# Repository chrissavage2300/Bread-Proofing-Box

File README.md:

# Bread-Proofing-Box
A PID controlled bread proofing box with heater

<H3>Change log</H3>

<b>9/22/2020</b>After some consideration, I might just end up using a light bulb for a heater instead of the custom one. The one I wound by hand would be great for dehydrating stuff, but it would consume 600W! In open air, a 200W light bulb got pretty hot, so I think I may use a 40W to 60W bulb for such low temperatures. I dont know where else I could look for heater.

<b>9/19/2020</b> Output is now connected to the PID loop in code. After some minor adjustments on the bench, it seems to be working great!

<b>8/3/2020</b> Mile stone reached! I managed to dim a light after a few days worth of troubleshooting, I found out I needed a 4 Quad TRIAC. So the main TRIAC is now a BT138-600. I also had to change the output from timer 2 to stay low and then go high, essentially making this a constant off time circuit. Once I got that figured out, I then saw the proper sine waves!

<b>5/29/2020</b> Rotary Encoder Works. Timer 1 also works. Outputs also work. Waiting on Rev B.

<b>5/24/2020</b> A major error was found. The power IC's IC2 and 3 are backwards. I thought I fixed it from an older revision, but guess not. Either way the current board is a dud :(. Also the transformer doesnt fit either, so this is now in pause while I wait and do another PCB revision.

<b>5/11/2020</b> Added in documents to show heatsink calculations along with heater wire calculations

<b>5/11/2020</b> Idea: Timer function on screen, count down? Time Remaining. Have buzzer go off when "done". This would be useful for a hydrate function.

<b>5/08/2020</b>- Board sent to PCB maker.

<b>5/03/2020</b>-Initially started with a PIC16F15356 but realized that it may need more memory for running a glcd. Also may need more processing power and higher clock frequency's so I may go with a 18F26Q10. 

Also I may rethink the heater. It kind of smells like burning plastic when on, so I may design my own using Nichrome 60 wire

<b>4/28/2020</b>-Got mechanical encoder code working. Also stuck the heater in the box to get an idea of what kind of temps I could expect. It seemed to max out to around 114F and then the shutoff kicked in slightly after that. So the max temp should be around 120F. It took around 10 minutes to get up to this temp. Its not high enough for dehydration, but it is hot enough for bread making and yogurt making. Wonder how hot it would get if the over temp switch was bypassed. 

Display thoughts:
* Internal Temperature (°F)
* External Temperature (°F)
* Humidity (%)
* Run Time (HH:MM:SS)
* Set Temperature (°F)

More thoughts: I could use this box to dry soap.

Since I want to keep the integrity of the box, maybe I should mount the system on the top of the box. This way I can still use the box for storage when not in use. So have the heater fan on top and it can be a dual use fan for intake, and then have another fan on the opposite end on top for exhaust. 

<b>4/26/2020-Initial Idea</b>

Ideas/wants: Spawned from the sour dough book I have that talks about a storage box or a cooler along side a light to proof bread dough or proof sour dough starter. They use a light bulb, but my experience with bulbs is that they get pretty hot, almost to 90-100F. I only know this because I used them to start seeds as well. I had then begun to search around for heaters, initially I thought of winding my own using nichrome or kanthal wire, but deemed that too be unsafe as I could possibly touch it by accident.

Next I thought of using a cartridge heater, it could work but felt like it would be too inefficient. I finally settled on using just a small space heater. When this is done there is another added benefit: I can dehydrate food or make yogurt. I dont know yet what the lower and upper temperature bounds are of a 250W heater.

Features/Additions:
* A HDX 12 gallon storage bin is just big enough for the bowl I use and can fit a jar or two inside as well
* 250W 120VAC Heater from Walmart. Cant wait to take it apart! I have a suspicion its like the so called "100W 12V PTC heater" on ebay.
* I figure I'll add in an intake fan as well for cool or room temp air. Oh boy..if I wanted to cool the air that would be interesting. 
* Which suggests a dual PID of sorts. I dont have one PID working yet, but I have some code that might work thats unfinished. 
* PID 1 will control the heater
* Maybe have the heater fan run at 100% all the time and just be on/off control. 
  * Control Strategy
  1) PWM Will vary the heater to accommodate a set temperature.
  2) Heater Fan will Turn on or off depending on if its needed or not. So, if the heater is ramping up, the fan will come on. This suggests really long loop refresh times, maybe 10 seconds should be good. Its a small box.
  3) So if the box is at the set temperature, the heater will be at some value, and the fan will be circulating air pretty much. The heater doesnt need to be shut off in this case, but the duty cycle will be low probably. Maybe add in an input to shut the PID off but keep the fan on to circulate air? 
* Optional: Cool Air/Room temperature Air intake. Control scheme would probably be to turn on this fan if its get too hot and shut the heater off completely and just keep the recirculation fan running.   
* Complex Add on: 3D printed louver doors so heat isnt lost when the cooling fan isnt on. 
* Exhaust fan and intake fan. Heater fan will be the recirculation fan. 

IO List:
* Start Button
* Stop Button
* Quadrature Encoder Knob to select temperature
* Internal Analog Temperature (MCP 9700)
* External Analog Temperature
* Internal Analog Humidity
* Intake Fan-PWM or DO
* Exhaust Fan-DO
* Heater fan/Recirculation Fan-PWM or DO
* I2C Display, so 2 extra IO
* ZCD input to sync heater but this can be acommplished with extra circuitry too
* 32kHz Crystal for clock

Based on this, I would use one of the following PIC micro's
* PIC16F1773
* PIC16F15355
* ~~PIC18F24Q10~~
* ~~PIC18F24K40~~

The Box:

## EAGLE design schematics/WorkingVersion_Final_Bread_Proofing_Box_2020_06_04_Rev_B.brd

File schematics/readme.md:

Encoder adapter is an adapter to make it panel mountable. 

Page 1 and 2 have been seperated. Page 1 is the main board. Page 2 is the power.

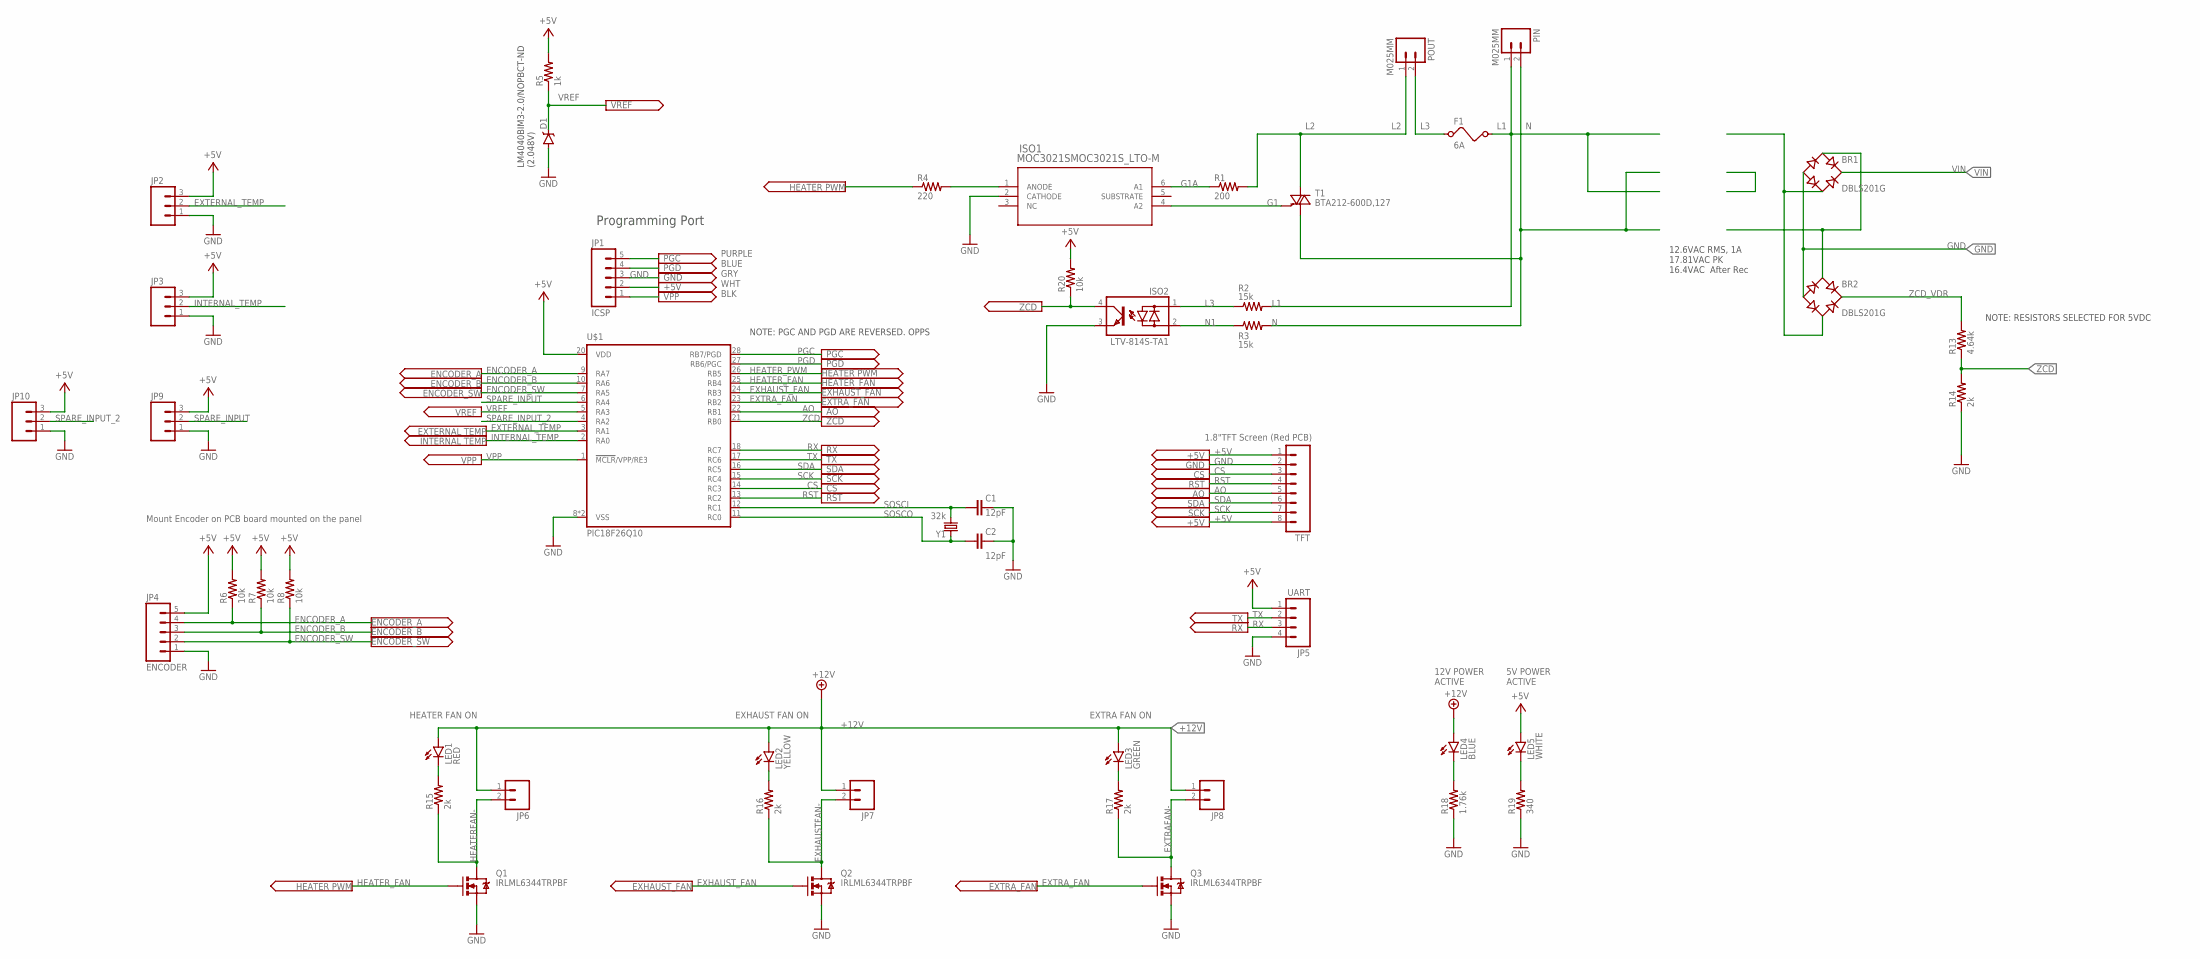
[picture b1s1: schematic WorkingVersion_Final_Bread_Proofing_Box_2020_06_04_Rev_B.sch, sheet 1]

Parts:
BR1, BR2: DBLS201G; DBS
C1, C2: 12pF; 0805
D1: V-REFERENCESMD; SOT23-3
F1: 6A; FUSE
ISO1: MOC3021SMOC3021S_LTO-M; MOC3021S_LTO-M
ISO2: LTV-814S-TA1; DIL4-SMD
JP1: ICSP; 1X05
JP2, JP3, JP9, JP10: M03POLAR; MOLEX-1X3
JP4: ENCODER; 1X05
JP5: UART; 1X04_LOCK
JP6, JP7, JP8: M02POLAR_LOCK; MOLEX-1X2_LOCK
LED1: RED; LED-1206
LED2: YELLOW; LED-1206
LED3: GREEN; LED-1206
LED4: BLUE; LED-1206
LED5: WHITE; LED-1206
PIN: M025MM; SCREWTERMINAL-5MM-2
POUT: M025MM; SCREWTERMINAL-5MM-2
Q1, Q2, Q3: IRLML6344TRPBF; SOT323
R1: 200; R2512
R2, R3: 15k; R2512
R4: 220; 1206
R5: 1k; 1206
R6, R7, R8, R20: 10k; 1206
R13: 4.64k; 1206
R14, R15, R16, R17: 2k; 1206
R18: 1.76k; 1206
R19: 340; 1206
T1: BTA212-600D,127; TO220BV
TFT: M08LOCK; 1X08_LOCK
U$1: PIC18F26Q10; SO28W
Y1: 32k; TC26V

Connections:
+5V: JP1.2, JP2.3, JP3.3, JP4.5, JP5.1, JP9.3, JP10.3, LED5.A, R5.2, R6.2, R7.2, R8.2, R20.2, TFT.1, TFT.8, U$1.20 (VDD); also elsewhere on the board
+12V: JP6.1, JP7.1, JP8.1, LED1.A, LED2.A, LED3.A, LED4.A; also elsewhere on the board
AO: TFT.5, U$1.22 (RB1)
CS: TFT.3, U$1.14 (RC3)
ENCODER_A: JP4.4, R6.1, U$1.9 (RA7)
ENCODER_B: JP4.3, R7.1, U$1.10 (RA6)
ENCODER_SW: JP4.2, R8.1, U$1.7 (RA5)
EXHAUSTFAN-: JP7.2, Q2.3 (D), R16.1
EXHAUST_FAN: Q2.1 (G), U$1.24 (RB3)
EXTERNAL_TEMP: JP2.2, U$1.3 (RA1)
EXTRAFAN-: JP8.2, Q3.3 (D), R17.1
EXTRA_FAN: Q3.1 (G), U$1.23 (RB2)
G1: ISO1.4 (A2), T1.G
G1A: ISO1.6 (A1), R1.1
GND: BR1.-, BR2.-, C1.2, C2.2, D1.2 (A), ISO1.2 (CATHODE), ISO2.3 (E), JP1.3, JP2.1, JP3.1, JP4.1, JP5.4, JP9.1, JP10.1, Q1.2 (S), Q2.2 (S), Q3.2 (S), R14.1, R18.1, R19.1, TFT.2, U$1.8 (VSS), U$1.19 (VSS); also elsewhere on the board
HEATERFAN-: JP6.2, Q1.3 (D), R15.1
HEATER_FAN: Q1.1 (G), U$1.25 (RB4)
HEATER_PWM: R4.1, U$1.26 (RB5)
INTERNAL_TEMP: JP3.2, U$1.2 (RA0)
L1: F1.2, PIN.1, R2.2
L2: POUT.1, R1.2, T1.T2 (A2)
L3: F1.1, ISO2.1 (AC1), POUT.2, R2.1
N: PIN.2, R3.2, T1.T1 (A1)
N1: ISO2.2 (AC2), R3.1
unnamed: ISO1.1 (ANODE), R4.2
unnamed: LED1.C, R15.2
unnamed: LED2.C, R16.2
unnamed: LED3.C, R17.2
unnamed: BR1.AC2, BR2.AC2
unnamed: BR1.AC1, BR2.AC1
unnamed: LED4.C, R18.2
unnamed: LED5.C, R19.2
PGC: JP1.5, U$1.28 (RB7/PGD)
PGD: JP1.4, U$1.27 (RB6/PGC)
RST: TFT.4, U$1.13 (RC2)
RX: JP5.3, U$1.18 (RC7)
SCK: TFT.7, U$1.15 (RC4)
SDA: TFT.6, U$1.16 (RC5)
SOSCI: C1.1, U$1.12 (RC1), Y1.1
SOSCO: C2.1, U$1.11 (RC0), Y1.2
SPARE_INPUT: JP9.2, U$1.6 (RA4)
SPARE_INPUT_2: JP10.2, U$1.4 (RA2)
TX: JP5.2, U$1.17 (RC6)
VIN: BR1.+; also elsewhere on the board
VPP: JP1.1, U$1.1 (!MCLR!/VPP/RE3)
VREF: D1.1 (C), R5.1, U$1.5 (RA3)
ZCD: ISO2.4 (C), R13.1, R14.2, R20.1, U$1.21 (RB0)
ZCD_VDR: BR2.+, R13.2

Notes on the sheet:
Programming Port
LM4040BIM3-2.0/NOPBCT-ND (2.048V)
1.8"TFT Screen (Red PCB)
12.6VAC RMS, 1A 17.81VAC PK 16.4VAC After Rec
Mount Encoder on PCB board mounted on the panel
12V POWER ACTIVE
5V POWER ACTIVE
HEATER FAN ON
EXHAUST FAN ON
EXTRA FAN ON
NOTE: RESISTORS SELECTED FOR 5VDC
NOTE: PGC AND PGD ARE REVERSED. OPPS
PURPLE BLUE GRY WHT BLK

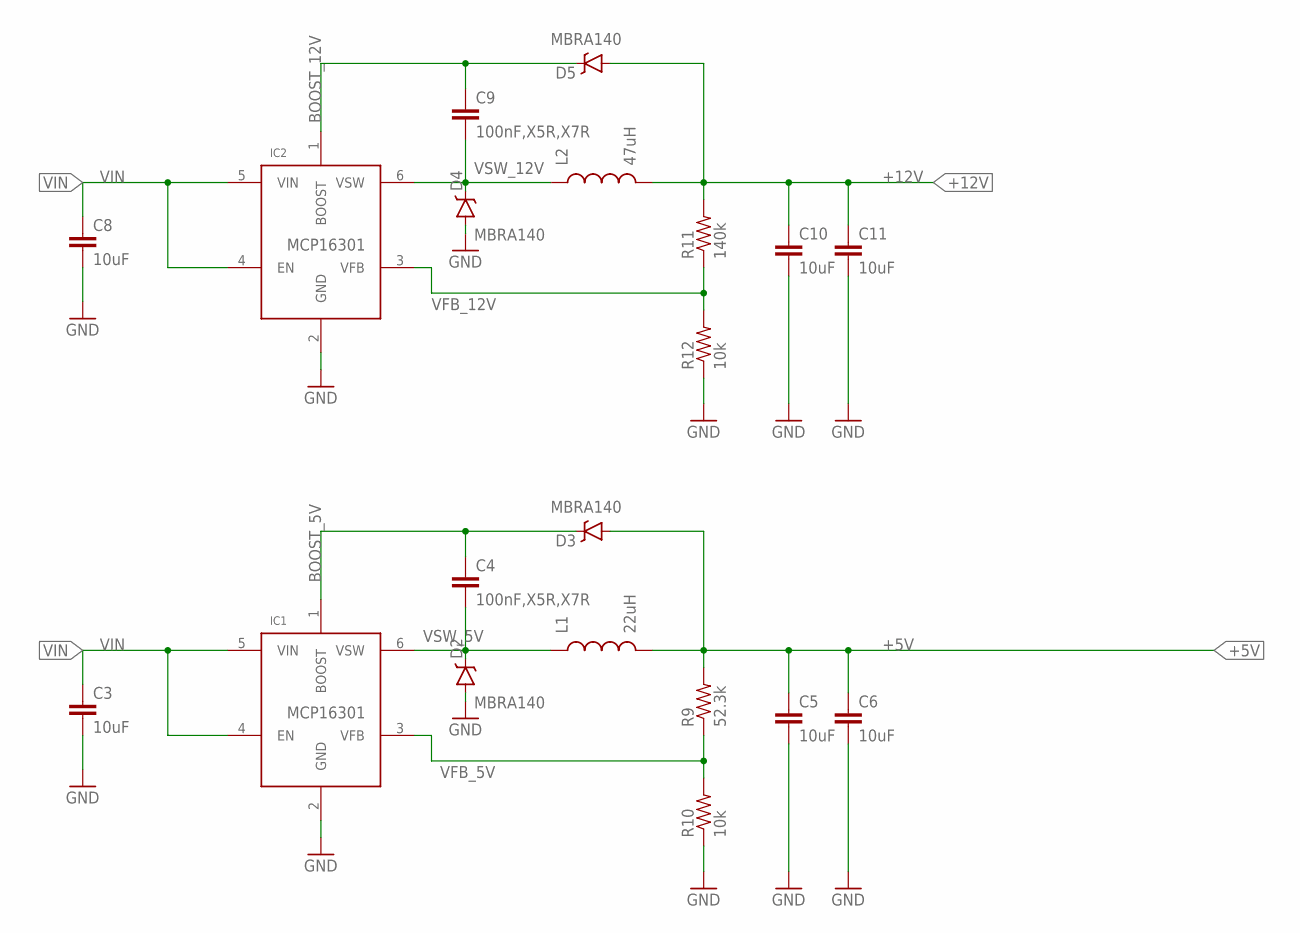
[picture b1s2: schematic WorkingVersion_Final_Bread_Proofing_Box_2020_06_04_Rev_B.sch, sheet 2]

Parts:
C3, C5, C6, C8, C10, C11: 10uF; 1206
C4, C9: 100nF,X5R,X7R; 1206
D2, D3, D4, D5: MBRA140; SMA-DIODE
IC1, IC2: MCP16301; SOT23-6
L1: 22uH; 1210
L2: 47uH; 1210
R9: 52.3k; 1206
R10, R12: 10k; 1206
R11: 140k; 1206

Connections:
+5V: C5.1, C6.1, D3.A, L1.2, R9.2; also elsewhere on the board
+12V: C10.1, C11.1, D5.A, L2.2, R11.2; also elsewhere on the board
BOOST_5V: C4.1, D3.C, IC1.1 (BOOST)
BOOST_12V: C9.1, D5.C, IC2.1 (BOOST)
GND: C3.2, C5.2, C6.2, C8.2, C10.2, C11.2, D2.A, D4.A, IC1.2 (GND), IC2.2 (GND), R10.1, R12.1; also elsewhere on the board
VFB_5V: IC1.3 (VFB), R9.1, R10.2
VFB_12V: IC2.3 (VFB), R11.1, R12.2
VIN: C3.1, C8.1, IC1.4 (EN), IC1.5 (VIN), IC2.4 (EN), IC2.5 (VIN); also elsewhere on the board
VSW_5V: C4.2, D2.C, IC1.6 (VSW), L1.1
VSW_12V: C9.2, D4.C, IC2.6 (VSW), L2.1

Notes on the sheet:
MCP16301

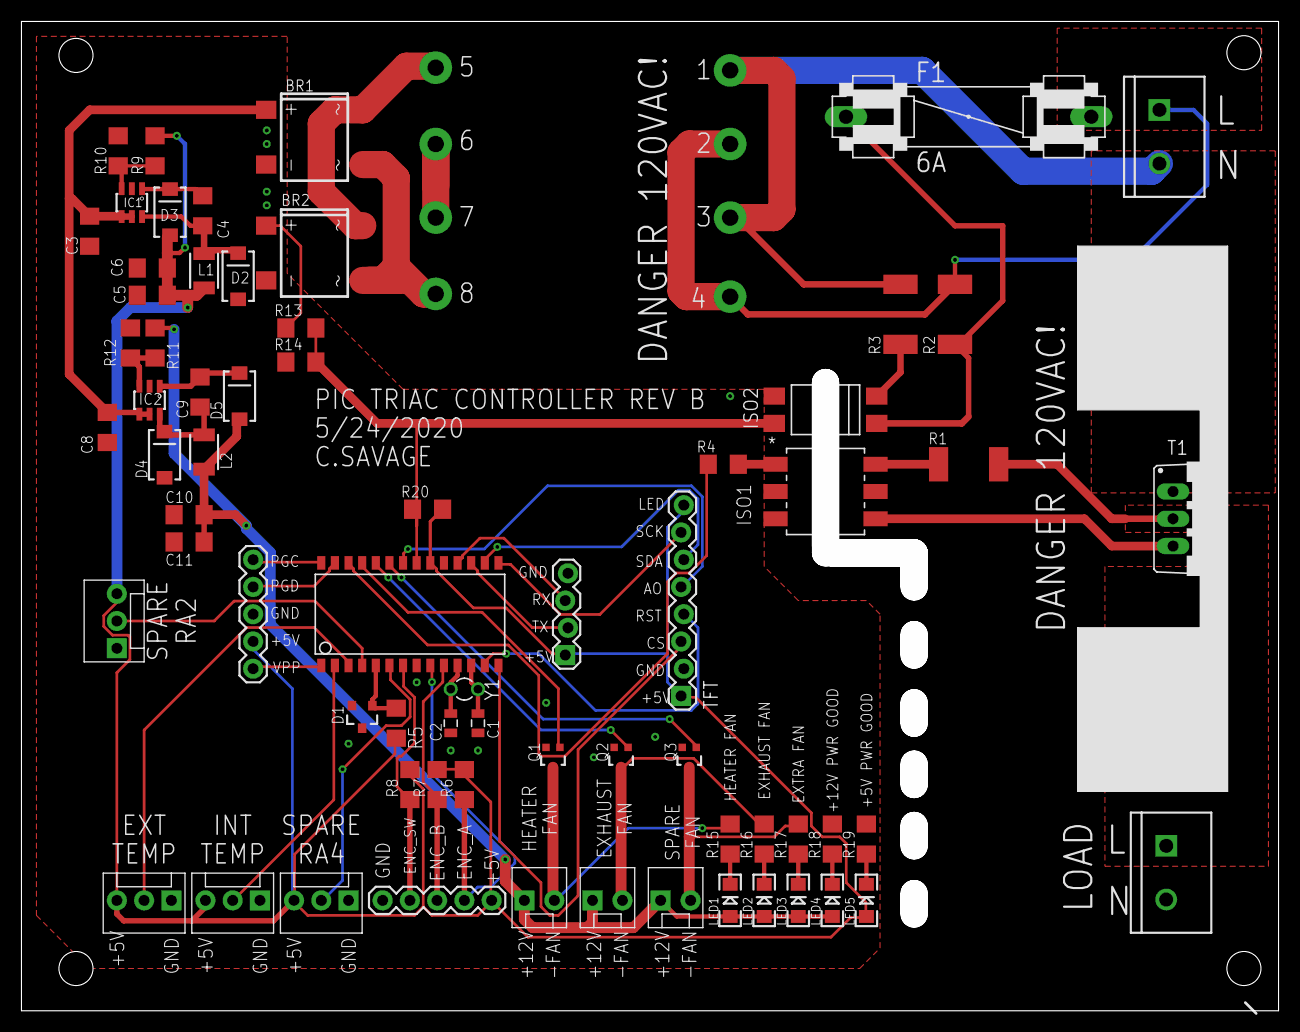
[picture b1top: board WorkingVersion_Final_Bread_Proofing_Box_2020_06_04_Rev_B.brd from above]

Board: 2 copper layers, 114.6 x 89.7 mm, 69 parts (0 on the bottom side), 54 nets.

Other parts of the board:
HEATSINK: 7-345-2PP-BA

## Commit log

2020-09-18 Add files via upload
    Working so far. Outputs and PID parameters are good.
2020-12-27 Add files via upload
    Testing/Working version as of 12/27/2020

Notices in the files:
parts and their libraries:
SparkFun-Capacitors: Licensing: Creative Commons ShareAlike 4.0 International - https://creativecommons.org/licenses/by-sa/4.0
COPYRIGHT: Copyright (C) 2018 Accelerated Designs. All rights reserved
